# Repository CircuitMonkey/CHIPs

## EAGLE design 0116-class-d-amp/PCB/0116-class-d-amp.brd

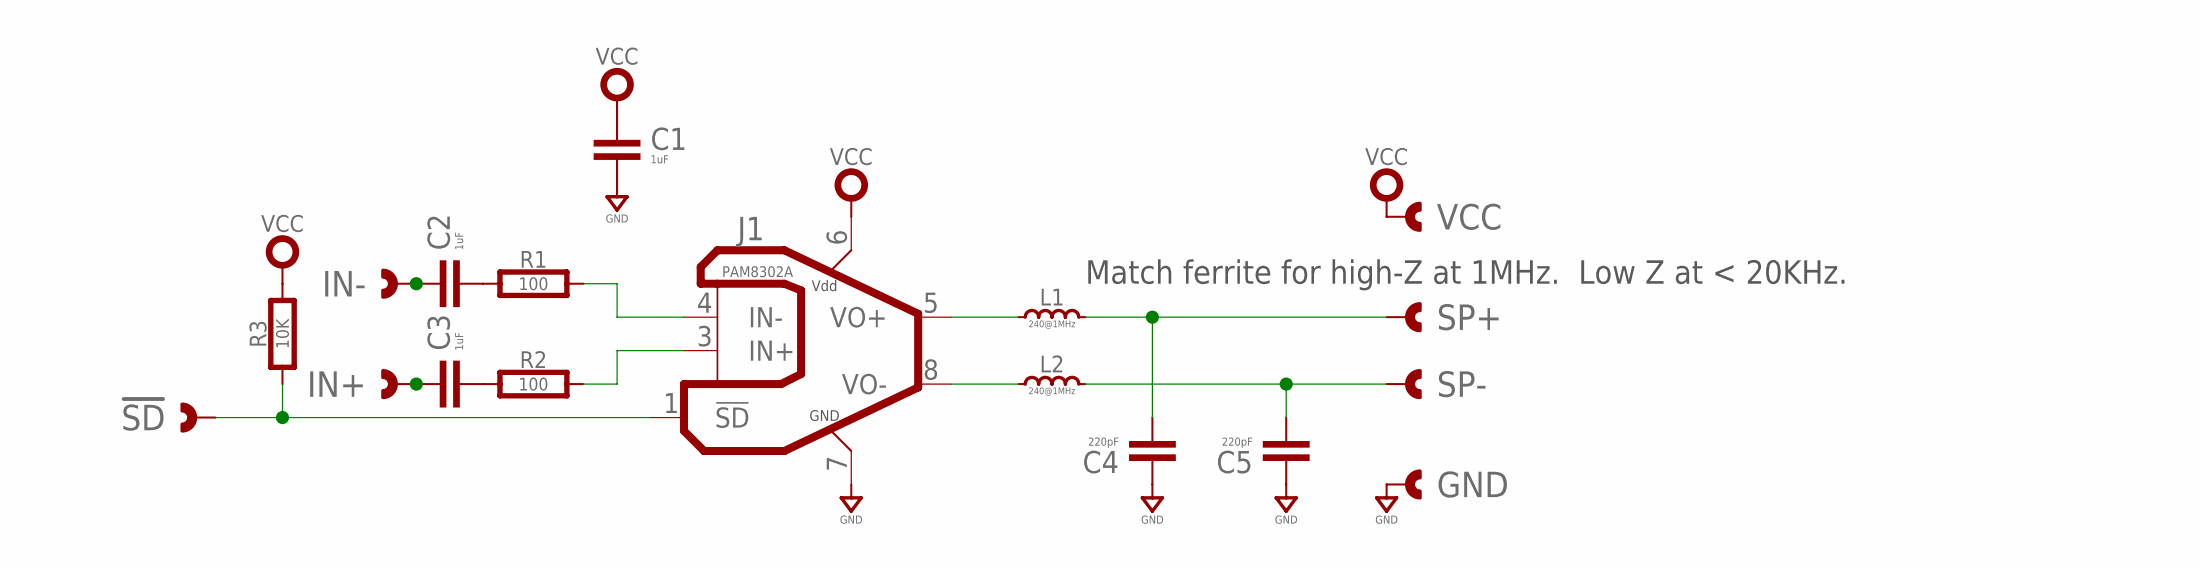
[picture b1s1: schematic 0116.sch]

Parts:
!SD: CAST-01X12.00MM; CAST01-2.00MM
C1, C2, C3: 1uF; 0402-CAP
C4, C5: 220pF; 0402-CAP
GND: CAST-01X12.00MM; CAST01-2.00MM
IN+: CAST-01X12.00MM; CAST01-2.00MM
IN-: CAST-01X12.00MM; CAST01-2.00MM
J1: PAM8302A; DFN-8-3X3
L1, L2: 240@1MHz; 0402-IND
R1, R2: 100; 0402-RES
R3: 10K; 0402-RES
SP+: CAST-01X12.00MM; CAST01-2.00MM
SP-: CAST-01X12.00MM; CAST01-2.00MM
VCC: CAST-01X12.00MM; CAST01-2.00MM

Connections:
!SD: !SD.1, !SD.P$1, !SD.P$2, J1.1 (!SD), R3.1
GND: C1.2, C4.1, C5.1, GND.1, GND.P$1, GND.P$2, J1.7 (GND)
unnamed: C2.2, R1.1
unnamed: C3.2, R2.1
unnamed: J1.4 (IN-), R1.2
unnamed: J1.3 (IN+), R2.2
unnamed: C4.2, L1.4 (2), SP+.1, SP+.P$1, SP+.P$2
unnamed: C2.1, IN-.1, IN-.P$1, IN-.P$2
unnamed: C3.1, IN+.1, IN+.P$1, IN+.P$2
unnamed: C5.2, L2.4 (2), SP-.1, SP-.P$1, SP-.P$2
unnamed: J1.5 (VO+), L1.3 (1)
unnamed: J1.8 (VO-), L2.3 (1)
VCC: C1.1, J1.6 (VDD), R3.2, VCC.1, VCC.P$1, VCC.P$2

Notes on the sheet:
Match ferrite for high-Z at 1MHz. Low Z at < 20KHz.

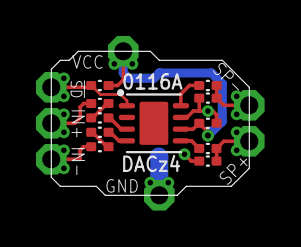
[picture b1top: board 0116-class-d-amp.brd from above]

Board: 2 copper layers, 11.0 x 8.0 mm, 18 parts (0 on the bottom side), 13 nets.

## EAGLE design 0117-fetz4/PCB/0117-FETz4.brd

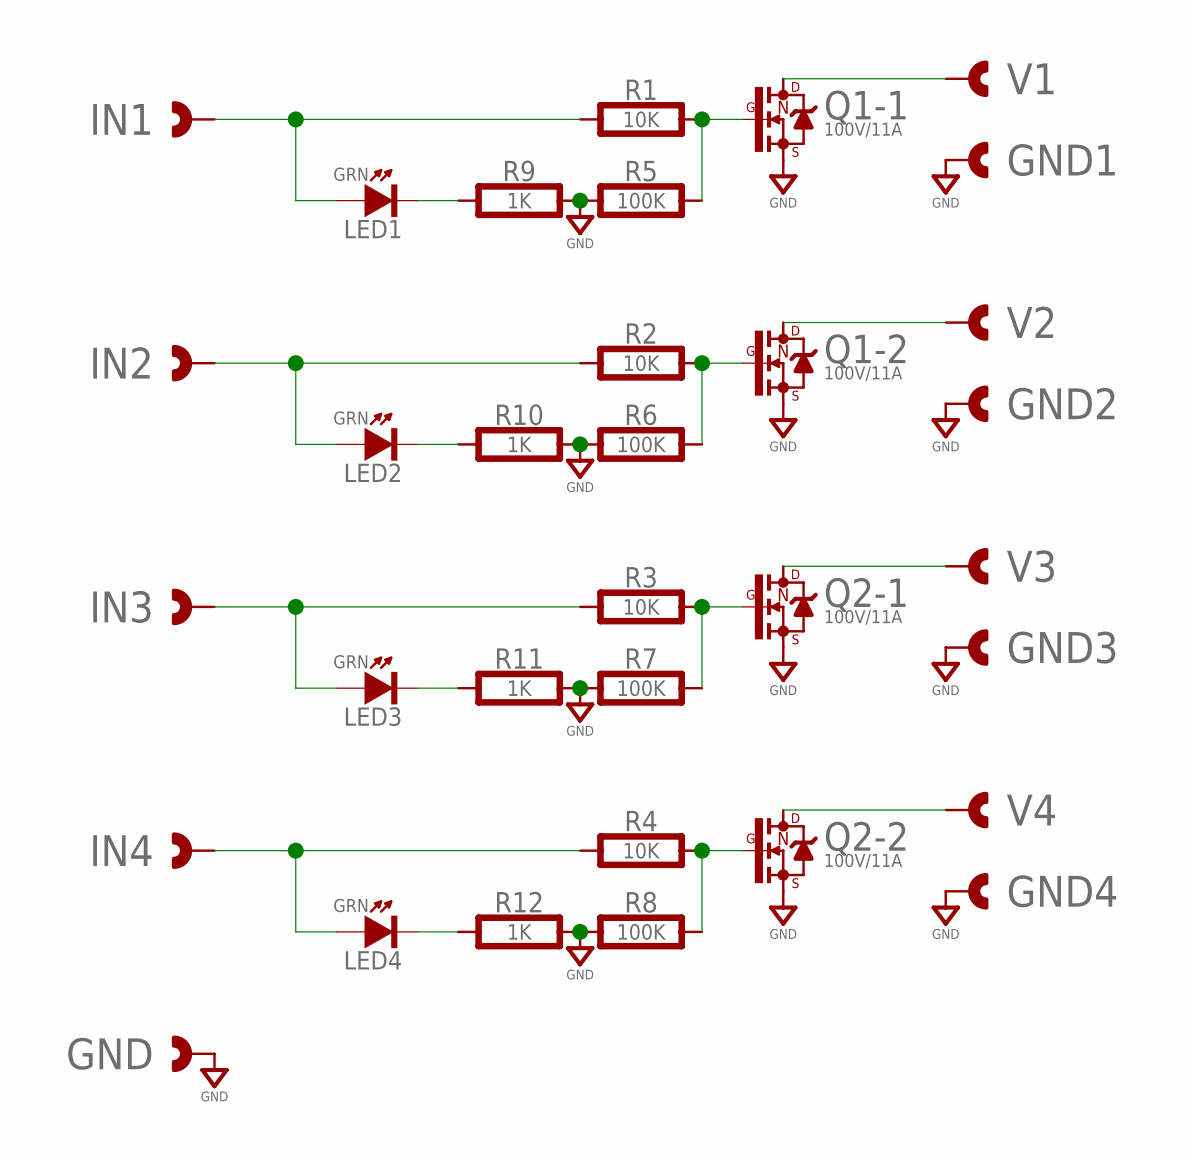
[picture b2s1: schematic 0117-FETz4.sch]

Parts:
GND, GND1, GND2, GND3, GND4: CAST-01X12.00MM; CAST01-2.00MM
IN1, IN2, IN3, IN4: CAST-01X12.00MM; CAST01-2.00MM
LED1, LED2, LED3, LED4: GRN; SMD_0603
Q1, Q2: 100V/11A; POWER_PAK-SO-8L-DUAL
R1, R2, R3, R4: 10K; 0603-RES
R5, R6, R7, R8: 100K; 0603-RES
R9, R10, R11, R12: 1K; 0603-RES
V1, V2, V3, V4: CAST-01X12.00MM; CAST01-2.00MM

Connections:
GND: GND.1, GND.P$1, GND.P$2, GND1.1, GND1.P$1, GND1.P$2, GND2.1, GND2.P$1, GND2.P$2, GND3.1, GND3.P$1, GND3.P$2, GND4.1, GND4.P$1, GND4.P$2, Q1.S1 (S), Q1.S2 (S), Q2.S1 (S), Q2.S2 (S), R5.1, R6.1, R7.1, R8.1, R9.2, R10.2, R11.2, R12.2
unnamed: Q1.D1 (D), Q1.D1B (D), Q1.D1C (D), V1.1, V1.P$1, V1.P$2
unnamed: LED1.K (C), R9.1
unnamed: Q1.D2 (D), Q1.D2B (D), Q1.D2C (D), V2.1, V2.P$1, V2.P$2
unnamed: Q2.D1 (D), Q2.D1B (D), Q2.D1C (D), V3.1, V3.P$1, V3.P$2
unnamed: LED2.K (C), R10.1
unnamed: Q2.D2 (D), Q2.D2B (D), Q2.D2C (D), V4.1, V4.P$1, V4.P$2
unnamed: IN1.1, IN1.P$1, IN1.P$2, LED1.A, R1.1
unnamed: IN2.1, IN2.P$1, IN2.P$2, LED2.A, R2.1
unnamed: IN3.1, IN3.P$1, IN3.P$2, LED3.A, R3.1
unnamed: IN4.1, IN4.P$1, IN4.P$2, LED4.A, R4.1
unnamed: Q1.G1 (G), R1.2, R5.2
unnamed: Q1.G2 (G), R2.2, R6.2
unnamed: Q2.G1 (G), R3.2, R7.2
unnamed: Q2.G2 (G), R4.2, R8.2
unnamed: LED3.K (C), R11.1
unnamed: LED4.K (C), R12.1

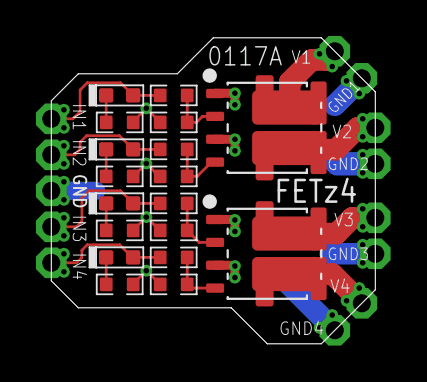
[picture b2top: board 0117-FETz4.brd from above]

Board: 2 copper layers, 18.0 x 17.0 mm, 31 parts (0 on the bottom side), 17 nets.

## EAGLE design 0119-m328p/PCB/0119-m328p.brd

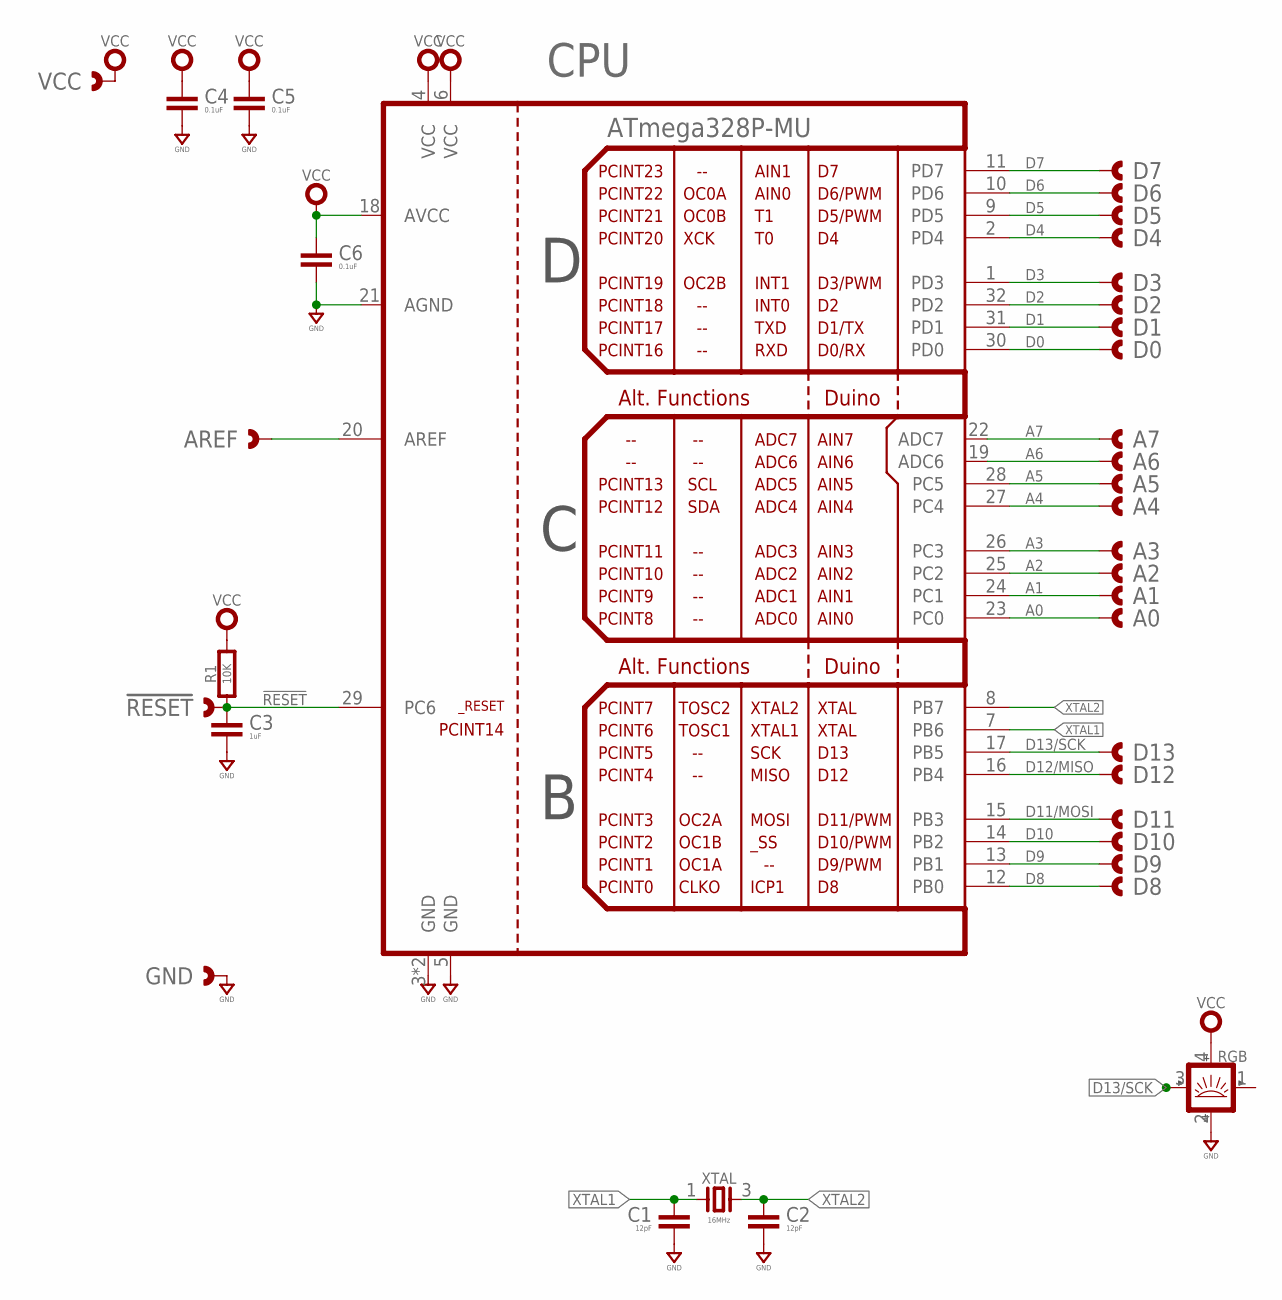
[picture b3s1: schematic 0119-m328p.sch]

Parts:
!RESET: CAST-01X12.00MM; CAST01-2.00MM
A0, A1, A2, A3, A4, A5, A6, A7: CAST-01X12.00MM; CAST01-2.00MM
AREF: CAST-01X12.00MM; CAST01-2.00MM
C1, C2: 12pF; 0402-CAP
C3: 1uF; 0402-CAP
C4, C5, C6: 0.1uF; 0402-CAP
CPU: ATmega328P-MU; MLF32
D0, D1, D2, D3, D4, D5, D6, D7, D8, D9, D10, D11, D12, D13: CAST-01X12.00MM; CAST01-2.00MM
GND: CAST-01X12.00MM; CAST01-2.00MM
R1: 10K; 0402-RES
RGB: SMART_LED2020; SMD_2020
VCC: CAST-01X12.00MM; CAST01-2.00MM
XTAL: 16MHz; 32X25

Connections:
!RESET: !RESET.1, !RESET.P$1, !RESET.P$2, C3.1, CPU.29 (PC6), R1.1
A0: A0.1, A0.P$1, A0.P$2, CPU.23 (PC0)
A1: A1.1, A1.P$1, A1.P$2, CPU.24 (PC1)
A2: A2.1, A2.P$1, A2.P$2, CPU.25 (PC2)
A3: A3.1, A3.P$1, A3.P$2, CPU.26 (PC3)
A4: A4.1, A4.P$1, A4.P$2, CPU.27 (PC4)
A5: A5.1, A5.P$1, A5.P$2, CPU.28 (PC5)
A6: A6.1, A6.P$1, A6.P$2, CPU.19 (ADC6)
A7: A7.1, A7.P$1, A7.P$2, CPU.22 (ADC7)
D0: CPU.30 (PD0), D0.1, D0.P$1, D0.P$2
D1: CPU.31 (PD1), D1.1, D1.P$1, D1.P$2
D2: CPU.32 (PD2), D2.1, D2.P$1, D2.P$2
D3: CPU.1 (PD3), D3.1, D3.P$1, D3.P$2
D4: CPU.2 (PD4), D4.1, D4.P$1, D4.P$2
D5: CPU.9 (PD5), D5.1, D5.P$1, D5.P$2
D6: CPU.10 (PD6), D6.1, D6.P$1, D6.P$2
D7: CPU.11 (PD7), D7.1, D7.P$1, D7.P$2
D8: CPU.12 (PB0), D8.1, D8.P$1, D8.P$2
D9: CPU.13 (PB1), D9.1, D9.P$1, D9.P$2
D10: CPU.14 (PB2), D10.1, D10.P$1, D10.P$2
D11/MOSI: CPU.15 (PB3), D11.1, D11.P$1, D11.P$2
D12/MISO: CPU.16 (PB4), D12.1, D12.P$1, D12.P$2
D13/SCK: CPU.17 (PB5), D13.1, D13.P$1, D13.P$2, RGB.3 (IN)
GND: C1.2, C2.2, C3.2, C4.2, C5.2, C6.2, CPU.3 (GND), CPU.5 (GND), CPU.21 (AGND), CPU.PAD (GND), GND.1, GND.P$1, GND.P$2, RGB.2 (GND)
unnamed: AREF.1, AREF.P$1, AREF.P$2, CPU.20 (AREF)
VCC: C4.1, C5.1, C6.1, CPU.4 (VCC), CPU.6 (VCC), CPU.18 (AVCC), R1.2, RGB.4 (VDD), VCC.1, VCC.P$1, VCC.P$2
XTAL1: C1.1, CPU.7 (PB6), XTAL.1
XTAL2: C2.1, CPU.8 (PB7), XTAL.3

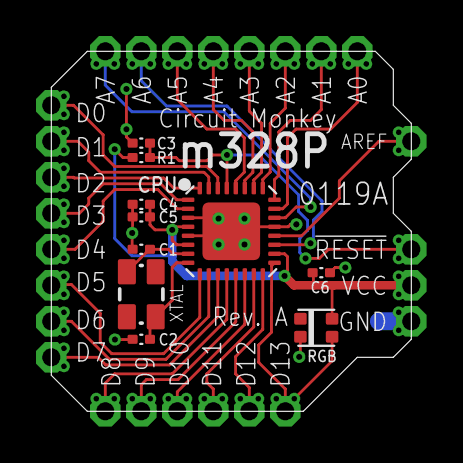
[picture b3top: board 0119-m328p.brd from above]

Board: 2 copper layers, 20.0 x 20.0 mm, 36 parts (0 on the bottom side), 28 nets.

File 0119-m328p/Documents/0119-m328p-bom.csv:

"Part";"Value";"Device";"Package";"Description";"MF";"MFR";"MPN";"OC_MOUSER";"OC_SEEED";"VALUE";
"!RESET";"CAST-01X12.00MM";"CAST-01X12.00MM";"CAST01-2.00MM";"Castelated Edge Hole Pad";"";"";"";"";"";"";
"A0";"CAST-01X12.00MM";"CAST-01X12.00MM";"CAST01-2.00MM";"Castelated Edge Hole Pad";"";"";"";"";"";"";
"A1";"CAST-01X12.00MM";"CAST-01X12.00MM";"CAST01-2.00MM";"Castelated Edge Hole Pad";"";"";"";"";"";"";
"A2";"CAST-01X12.00MM";"CAST-01X12.00MM";"CAST01-2.00MM";"Castelated Edge Hole Pad";"";"";"";"";"";"";
"A3";"CAST-01X12.00MM";"CAST-01X12.00MM";"CAST01-2.00MM";"Castelated Edge Hole Pad";"";"";"";"";"";"";
"A4";"CAST-01X12.00MM";"CAST-01X12.00MM";"CAST01-2.00MM";"Castelated Edge Hole Pad";"";"";"";"";"";"";
"A5";"CAST-01X12.00MM";"CAST-01X12.00MM";"CAST01-2.00MM";"Castelated Edge Hole Pad";"";"";"";"";"";"";
"A6";"CAST-01X12.00MM";"CAST-01X12.00MM";"CAST01-2.00MM";"Castelated Edge Hole Pad";"";"";"";"";"";"";
"A7";"CAST-01X12.00MM";"CAST-01X12.00MM";"CAST01-2.00MM";"Castelated Edge Hole Pad";"";"";"";"";"";"";
"AREF";"CAST-01X12.00MM";"CAST-01X12.00MM";"CAST01-2.00MM";"Castelated Edge Hole Pad";"";"";"";"";"";"";
"C1";"12pF";"CAPACITOR0402";"0402-CAP";"Capacitor";"";"";"";"";"";"";
"C2";"12pF";"CAPACITOR0402";"0402-CAP";"Capacitor";"";"";"";"";"";"";
"C3";"1uF";"CAPACITOR0402";"0402-CAP";"Capacitor";"";"";"";"";"";"";
"C4";"0.1uF";"CAPACITOR0402";"0402-CAP";"Capacitor";"";"";"";"";"";"";
"C5";"0.1uF";"CAPACITOR0402";"0402-CAP";"Capacitor";"";"";"";"";"";"";
"C6";"0.1uF";"CAPACITOR0402";"0402-CAP";"Capacitor";"";"";"";"";"";"";
"CPU";"ATmega328P-MU";"ATMEGA328MU";"MLF32";"Atmega 328P";"";"Atmel";"atmega328p-mu";"556-ATMEGA328P-MU";"310010005";"ATmega328P-MU";
"D0";"CAST-01X12.00MM";"CAST-01X12.00MM";"CAST01-2.00MM";"Castelated Edge Hole Pad";"";"";"";"";"";"";
"D1";"CAST-01X12.00MM";"CAST-01X12.00MM";"CAST01-2.00MM";"Castelated Edge Hole Pad";"";"";"";"";"";"";
"D2";"CAST-01X12.00MM";"CAST-01X12.00MM";"CAST01-2.00MM";"Castelated Edge Hole Pad";"";"";"";"";"";"";
"D3";"CAST-01X12.00MM";"CAST-01X12.00MM";"CAST01-2.00MM";"Castelated Edge Hole Pad";"";"";"";"";"";"";
"D4";"CAST-01X12.00MM";"CAST-01X12.00MM";"CAST01-2.00MM";"Castelated Edge Hole Pad";"";"";"";"";"";"";
"D5";"CAST-01X12.00MM";"CAST-01X12.00MM";"CAST01-2.00MM";"Castelated Edge Hole Pad";"";"";"";"";"";"";
"D6";"CAST-01X12.00MM";"CAST-01X12.00MM";"CAST01-2.00MM";"Castelated Edge Hole Pad";"";"";"";"";"";"";
"D7";"CAST-01X12.00MM";"CAST-01X12.00MM";"CAST01-2.00MM";"Castelated Edge Hole Pad";"";"";"";"";"";"";
"D8";"CAST-01X12.00MM";"CAST-01X12.00MM";"CAST01-2.00MM";"Castelated Edge Hole Pad";"";"";"";"";"";"";
"D9";"CAST-01X12.00MM";"CAST-01X12.00MM";"CAST01-2.00MM";"Castelated Edge Hole Pad";"";"";"";"";"";"";
"D10";"CAST-01X12.00MM";"CAST-01X12.00MM";"CAST01-2.00MM";"Castelated Edge Hole Pad";"";"";"";"";"";"";
"D11";"CAST-01X12.00MM";"CAST-01X12.00MM";"CAST01-2.00MM";"Castelated Edge Hole Pad";"";"";"";"";"";"";
"D12";"CAST-01X12.00MM";"CAST-01X12.00MM";"CAST01-2.00MM";"Castelated Edge Hole Pad";"";"";"";"";"";"";
"D13";"CAST-01X12.00MM";"CAST-01X12.00MM";"CAST01-2.00MM";"Castelated Edge Hole Pad";"";"";"";"";"";"";
"GND";"CAST-01X12.00MM";"CAST-01X12.00MM";"CAST01-2.00MM";"Castelated Edge Hole Pad";"";"";"";"";"";"";
"R1";"10K";"RESISTOR0402";"0402-RES";"Resistor";"";"";"";"";"";"";
"RGB";"";"SMART_LED2020";"SMD_2020";"Smart LED  SK6812  WS2812";"";"";"";"";"";"";
"VCC";"CAST-01X12.00MM";"CAST-01X12.00MM";"CAST01-2.00MM";"Castelated Edge Hole Pad";"";"";"";"";"";"";
"XTAL";"16MHz";"2P3.2X2.5";"32X25";"Crystal";"Epson";"";"FA-238 16.0000MB-K3";"";"";"16MHz";

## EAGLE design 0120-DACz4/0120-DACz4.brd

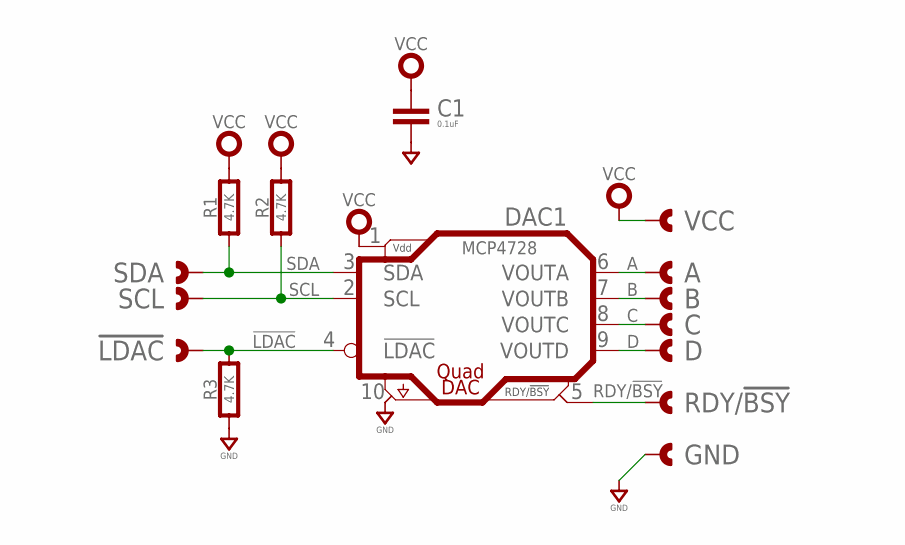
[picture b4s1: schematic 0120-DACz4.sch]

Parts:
!LDAC: CAST-01X12.00MM; CAST01-2.00MM
A: CAST-01X12.00MM; CAST01-2.00MM
B: CAST-01X12.00MM; CAST01-2.00MM
C: CAST-01X12.00MM; CAST01-2.00MM
C1: 0.1uF; 0603-CAP
D: CAST-01X12.00MM; CAST01-2.00MM
DAC1: MCP4728; MSOP10
GND: CAST-01X12.00MM; CAST01-2.00MM
R1, R2, R3: 4.7K; 0603-RES
RDY/!BSY: CAST-01X12.00MM; CAST01-2.00MM
SCL: CAST-01X12.00MM; CAST01-2.00MM
SDA: CAST-01X12.00MM; CAST01-2.00MM
VCC: CAST-01X12.00MM; CAST01-2.00MM

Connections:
!LDAC: !LDAC.1, !LDAC.P$1, !LDAC.P$2, DAC1.4 (!LDAC), R3.2
A: A.1, A.P$1, A.P$2, DAC1.6 (VOUTA)
B: B.1, B.P$1, B.P$2, DAC1.7 (VOUTB)
C: C.1, C.P$1, C.P$2, DAC1.8 (VOUTC)
D: D.1, D.P$1, D.P$2, DAC1.9 (VOUTD)
GND: C1.2, DAC1.10 (GND), GND.1, GND.P$1, GND.P$2, R3.1
RDY/!BSY: DAC1.5 (RDY/!BSY), RDY/!BSY.1, RDY/!BSY.P$1, RDY/!BSY.P$2
SCL: DAC1.2 (SCL), R2.1, SCL.1, SCL.P$1, SCL.P$2
SDA: DAC1.3 (SDA), R1.1, SDA.1, SDA.P$1, SDA.P$2
VCC: C1.1, DAC1.1 (VDD), R1.2, R2.2, VCC.1, VCC.P$1, VCC.P$2

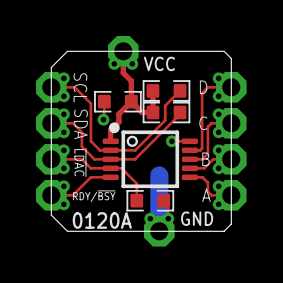
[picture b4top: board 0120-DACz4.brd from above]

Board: 2 copper layers, 10.0 x 10.0 mm, 15 parts (0 on the bottom side), 10 nets.

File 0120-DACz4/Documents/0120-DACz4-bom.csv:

"Part";"Value";"Device";"Package";"Description";"MFR";"MPN";"VALUE";
"!LDAC";"CAST-01X12.00MM";"CAST-01X12.00MM";"CAST01-2.00MM";"Castelated Edge Hole Pad";"";"";"";
"A";"CAST-01X12.00MM";"CAST-01X12.00MM";"CAST01-2.00MM";"Castelated Edge Hole Pad";"";"";"";
"B";"CAST-01X12.00MM";"CAST-01X12.00MM";"CAST01-2.00MM";"Castelated Edge Hole Pad";"";"";"";
"C";"CAST-01X12.00MM";"CAST-01X12.00MM";"CAST01-2.00MM";"Castelated Edge Hole Pad";"";"";"";
"C1";"0.1uF";"CAPACITOR0603";"0603-CAP";"Capacitor";"";"";"";
"D";"CAST-01X12.00MM";"CAST-01X12.00MM";"CAST01-2.00MM";"Castelated Edge Hole Pad";"";"";"";
"DAC1";"MCP4728";"MCP4728";"MSOP10";"Quad DAC with I2C";"Microchip";"MCP4728";"MCP4728";
"GND";"CAST-01X12.00MM";"CAST-01X12.00MM";"CAST01-2.00MM";"Castelated Edge Hole Pad";"";"";"";
"R1";"4.7K";"RESISTOR0603";"0603-RES";"Resistor";"";"";"";
"R2";"4.7K";"RESISTOR0603";"0603-RES";"Resistor";"";"";"";
"R3";"4.7K";"RESISTOR0603";"0603-RES";"Resistor";"";"";"";
"RDY/!BSY";"CAST-01X12.00MM";"CAST-01X12.00MM";"CAST01-2.00MM";"Castelated Edge Hole Pad";"";"";"";
"SCL";"CAST-01X12.00MM";"CAST-01X12.00MM";"CAST01-2.00MM";"Castelated Edge Hole Pad";"";"";"";
"SDA";"CAST-01X12.00MM";"CAST-01X12.00MM";"CAST01-2.00MM";"Castelated Edge Hole Pad";"";"";"";
"VCC";"CAST-01X12.00MM";"CAST-01X12.00MM";"CAST01-2.00MM";"Castelated Edge Hole Pad";"";"";"";

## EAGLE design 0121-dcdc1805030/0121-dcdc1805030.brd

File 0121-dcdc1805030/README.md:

# Circuit Monkey CHIPs &#35;0121 -- DCDC Converter 5V@3A

## Images

## Technical Details
* **Dimensions:** 10mm wide x 9mm tall  x 1.6mm PCB thickness
* **Pad Style:** Castellated Pin Edges allow easy surface mounting as well as hand wiring
* **Pad Pitch:** Minimum Pad Pitch is 2.0mm
* **Amplifier:** Diodes Inc. [AP62300 DCDC Converter](https://www.diodes.com/assets/Datasheets/AP62300_AP62301_AP62300T.pdf)

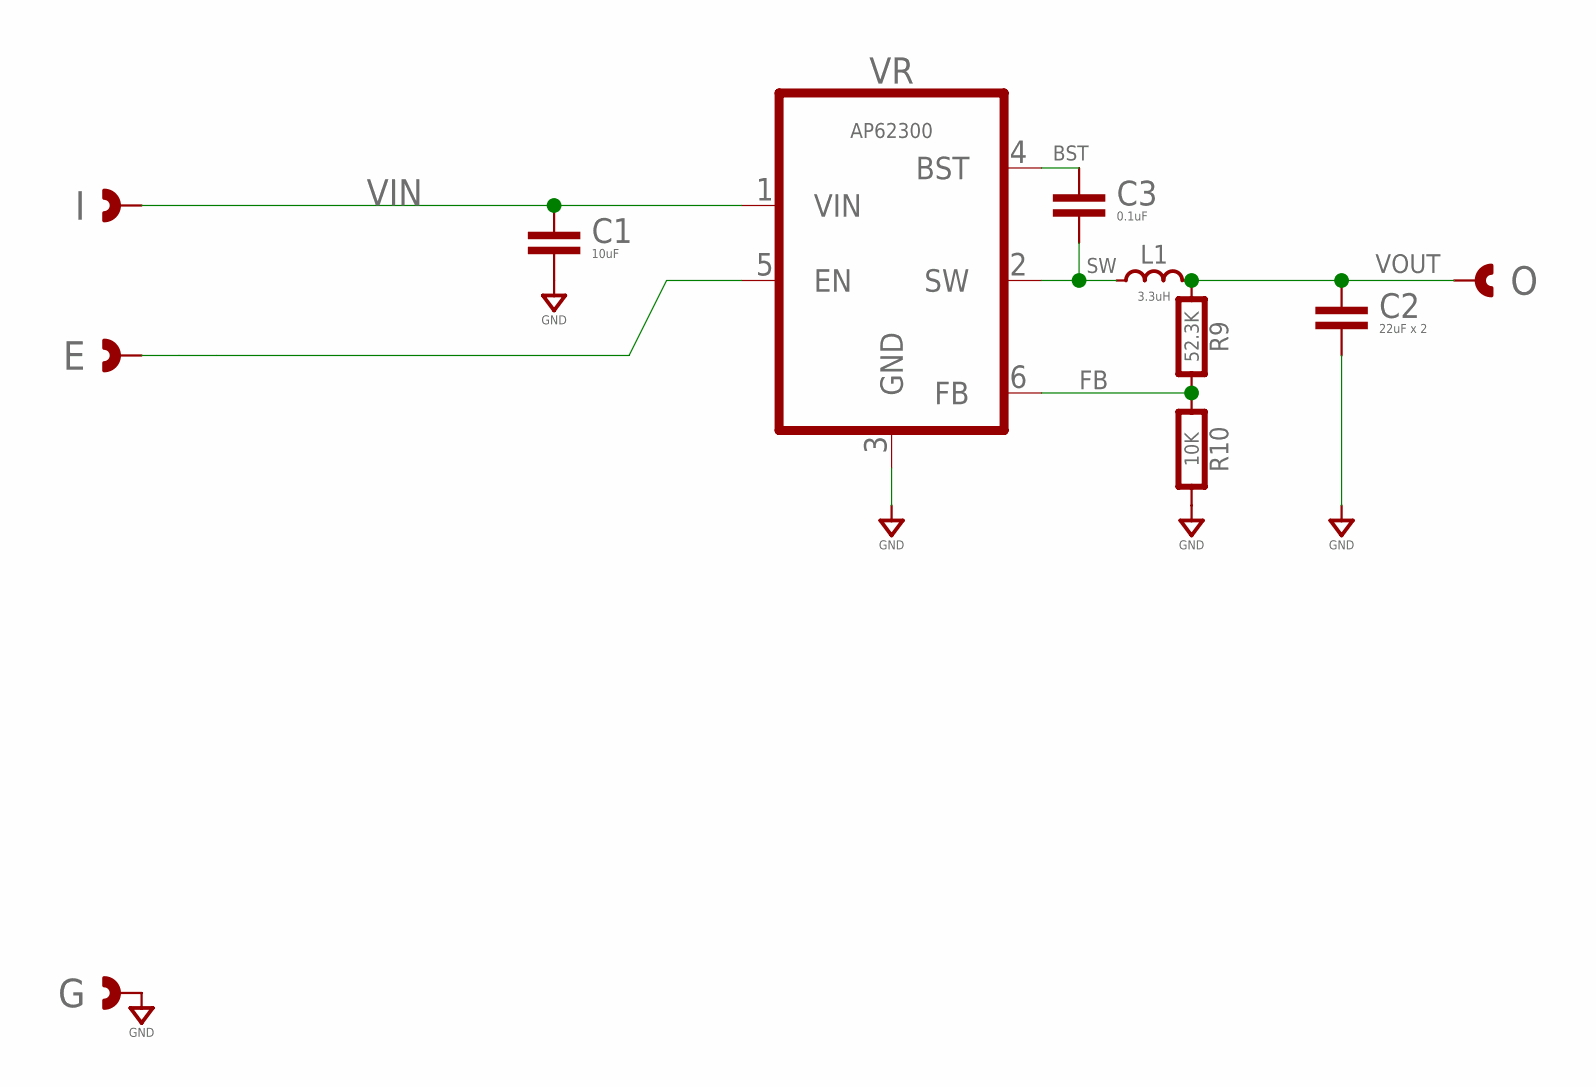
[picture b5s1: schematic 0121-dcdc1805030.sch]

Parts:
C1: 10uF; 0603-CAP
C2: 22uF x 2; 0603-CAP
C3: 0.1uF; 0603-CAP
E: CAST-01X12.00MM; CAST01-2.00MM
G: CAST-01X12.00MM; CAST01-2.00MM
I: CAST-01X12.00MM; CAST01-2.00MM
L1: 3.3uH; IND-SRN5040; MPN SRN5040-3R3M
O: CAST-01X12.00MM; CAST01-2.00MM
R9: 52.3K; 0603-RES
R10: 10K; 0603-RES
VR: AP62300; SOT-563-6

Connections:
BST: C3.1, VR.4 (BST)
FB: R9.2, R10.1, VR.6 (FB)
GND: C1.2, C2.2, G.1, G.P$1, G.P$2, R10.2, VR.3 (GND)
unnamed: E.1, E.P$1, E.P$2, VR.5 (EN)
SW: C3.2, L1.2, VR.2 (SW)
VIN: C1.1, I.1, I.P$1, I.P$2, VR.1 (VIN)
VOUT: C2.1, L1.1, O.1, O.P$1, O.P$2, R9.1

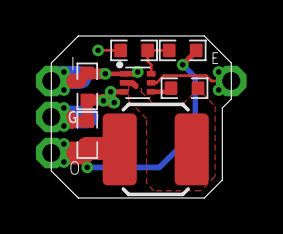
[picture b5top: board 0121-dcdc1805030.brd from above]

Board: 2 copper layers, 10.0 x 9.0 mm, 11 parts (0 on the bottom side), 7 nets.

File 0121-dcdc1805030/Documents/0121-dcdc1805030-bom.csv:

"Part";"Value";"Device";"Package";"Description";"COST01";"MFR";"MPN";"VALUE";
"C1";"10uF";"CAPACITOR0603";"0603-CAP";"Capacitor";"";"";"";"";
"C2";"22uF x 2";"CAPACITOR0603";"0603-CAP";"Capacitor";"";"";"";"";
"C3";"0.1uF";"CAPACITOR0603";"0603-CAP";"Capacitor";"";"";"";"";
"E";"CAST-01X12.00MM";"CAST-01X12.00MM";"CAST01-2.00MM";"Castelated Edge Hole Pad";"";"";"";"";
"G";"CAST-01X12.00MM";"CAST-01X12.00MM";"CAST01-2.00MM";"Castelated Edge Hole Pad";"";"";"";"";
"I";"CAST-01X12.00MM";"CAST-01X12.00MM";"CAST01-2.00MM";"Castelated Edge Hole Pad";"";"";"";"";
"L1";"3.3uH";"INDUCTORSMD-05X04MM";"IND-SRN5040";"Inductor";"";"Bourns";"SRN5040-3R3M";"";
"O";"CAST-01X12.00MM";"CAST-01X12.00MM";"CAST01-2.00MM";"Castelated Edge Hole Pad";"";"";"";"";
"R9";"52.3K";"RESISTOR0603";"0603-RES";"Resistor";"";"";"";"";
"R10";"10K";"RESISTOR0603";"0603-RES";"Resistor";"";"";"";"";
"VR";"AP62300";"BUCKAP62300";"SOT-563-6";"Buck Regulator";"0.50";"Diodes, Inc.";"AP62301Z6-7";"AP62300";
